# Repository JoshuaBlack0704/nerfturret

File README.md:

# nerfturret
Mechatronics class project

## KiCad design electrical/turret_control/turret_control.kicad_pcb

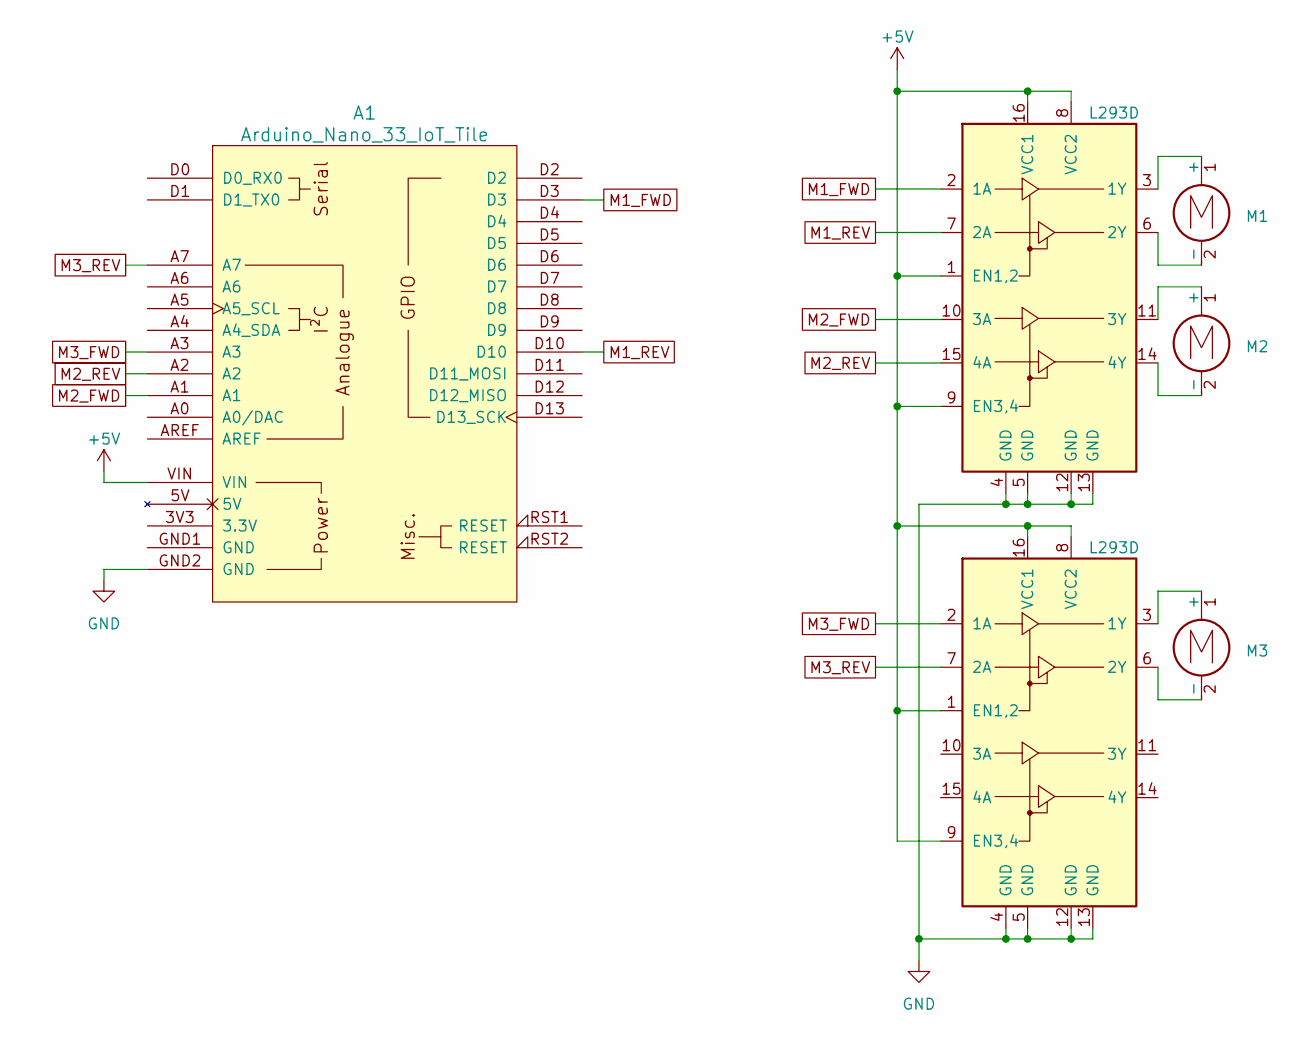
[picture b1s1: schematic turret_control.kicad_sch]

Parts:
A1: Arduino_Nano_33_IoT_Tile; Arduino_Nano_33_IoT_Socket
M1, M2, M3: Motor_DC; PinHeader_1x02_P2.54mm_Vertical_SMD_Pin1Left
U1, U2: L293D; DIP-16_W7.62mm

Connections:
+5V: A1.VIN, U1.1 (EN1,2), U1.8 (VCC2), U1.9 (EN3,4), U1.16 (VCC1), U2.1 (EN1,2), U2.8 (VCC2), U2.9 (EN3,4), U2.16 (VCC1)
GND: A1.GND2 (GND), U1.4 (GND), U1.5 (GND), U1.12 (GND), U1.13 (GND), U2.4 (GND), U2.5 (GND), U2.12 (GND), U2.13 (GND)
M1_FWD: A1.D3, U1.2 (1A)
M1_REV: A1.D10, U1.7 (2A)
M2_FWD: A1.A1, U1.10 (3A)
M2_REV: A1.A2, U1.15 (4A)
M3_FWD: A1.A3, U2.2 (1A)
M3_REV: A1.A7, U2.7 (2A)
unnamed: M1.1 (+), U1.3 (1Y)
unnamed: M1.2 (-), U1.6 (2Y)
unnamed: M2.1 (+), U1.11 (3Y)
unnamed: M2.2 (-), U1.14 (4Y)
unnamed: M3.1 (+), U2.3 (1Y)
unnamed: M3.2 (-), U2.6 (2Y)

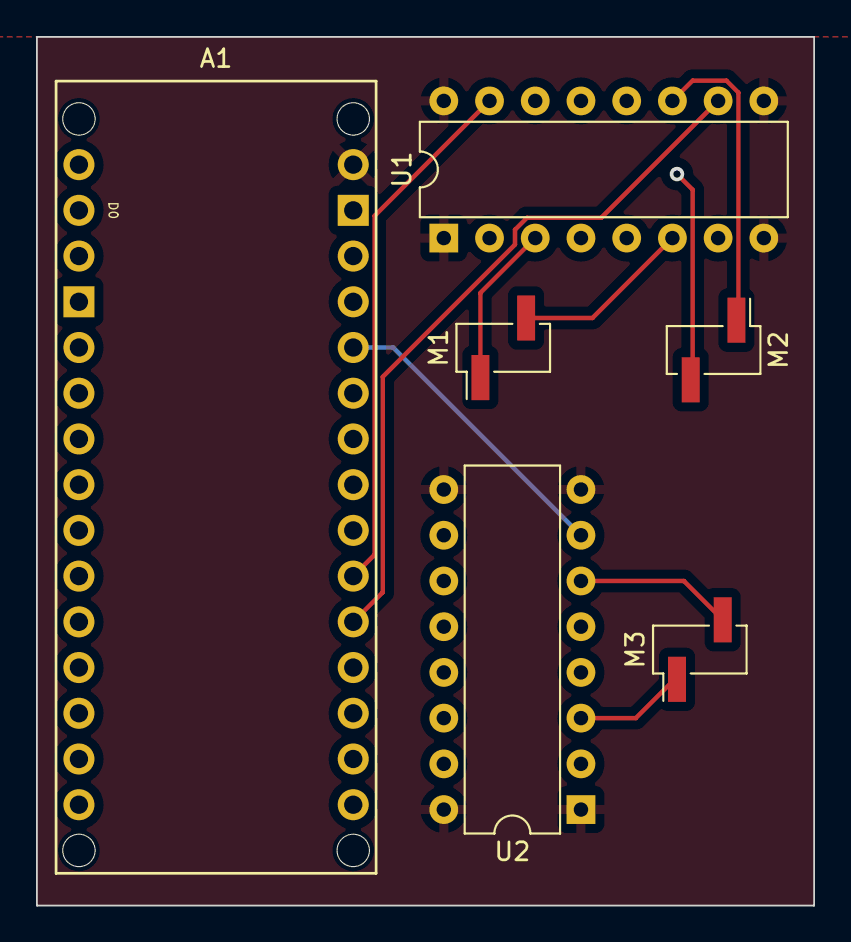
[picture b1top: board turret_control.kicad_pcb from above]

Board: 4 copper layers, 43.2 x 48.3 mm, 6 parts (0 on the bottom side), 14 nets.

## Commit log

2023-03-23 FreeCAD practice and scaling
2023-03-28 co2holder
2023-03-29 barrel cam
2023-03-29 motor mount
2023-03-30 parametrics
2023-03-31 side slide design
2023-04-03 Clip holder v1
2023-04-03 Slide changes
2023-04-10 Co2, holder
2023-04-16 Test assembly
2023-04-17 Base gear and plate
2023-04-17 Base mounting print
2023-04-18 Tilt axle holder and gear
2023-04-19 Payload Mount
2023-04-24 Resizing
2023-04-24 Co2 holder
2023-04-24 Mount Pin
2023-04-26 Finished cad design
2023-05-05 stl upload
2023-05-10 Working code set
2023-05-10 Final report
